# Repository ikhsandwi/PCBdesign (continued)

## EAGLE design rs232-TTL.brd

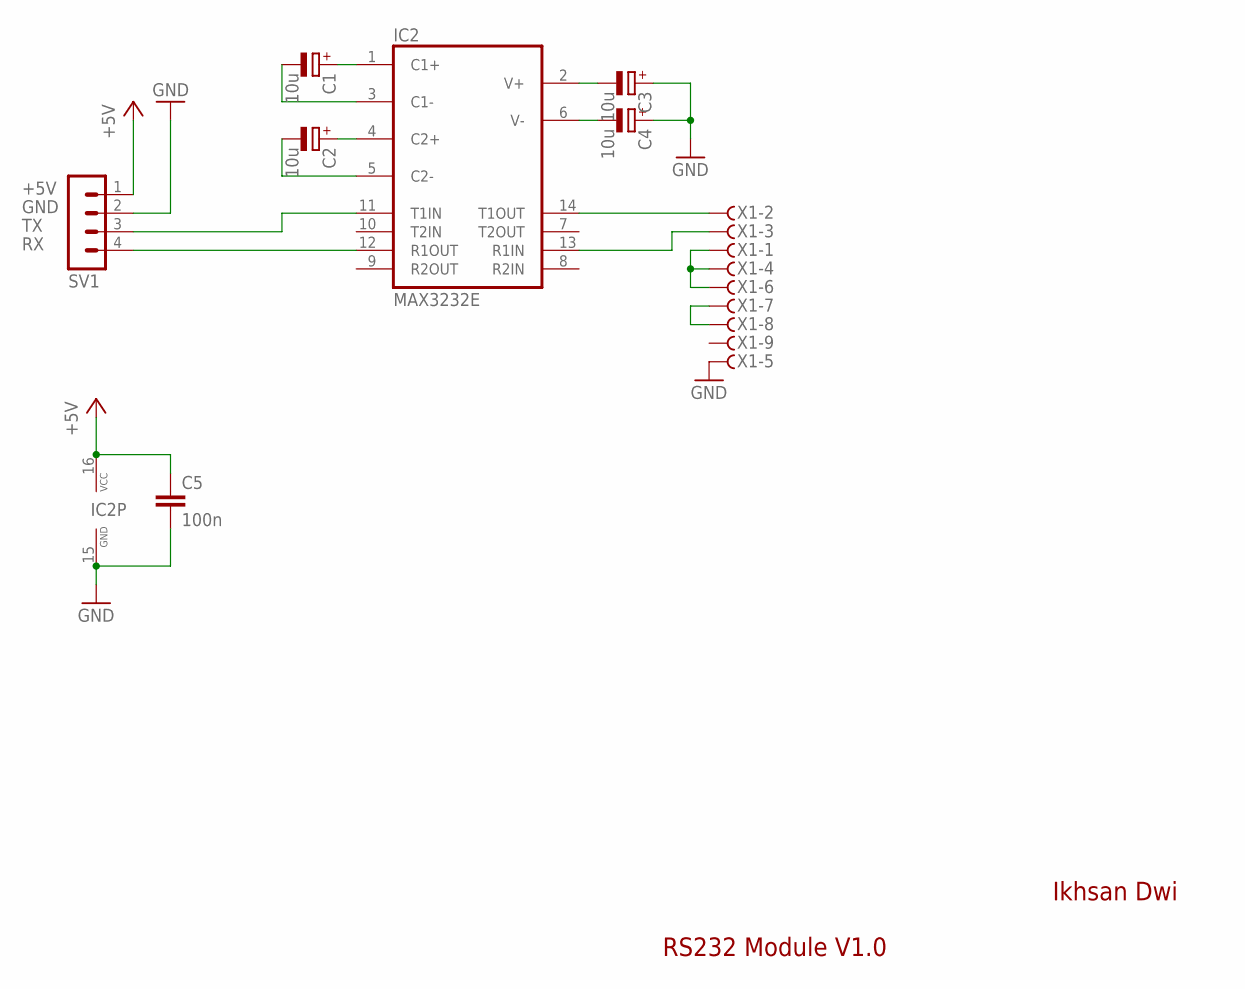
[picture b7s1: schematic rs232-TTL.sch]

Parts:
C1, C2, C3, C4: 10u; E2,5-6
C5: 100n; C050-024X044
IC2: MAX3232E; DIL16
SV1: MA04-1
X1: F09HS; F09H

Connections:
+5V: C5.1, IC2.16 (VCC), SV1.1
GND: C3.+, C4.+, C5.2, IC2.15 (GND), SV1.2, X1.5
unnamed: C1.-, IC2.3 (C1-)
unnamed: C1.+, IC2.1 (C1+)
unnamed: X1.1, X1.4, X1.6
unnamed: C2.+, IC2.4 (C2+)
unnamed: C2.-, IC2.5 (C2-)
unnamed: C3.-, IC2.2 (V+)
unnamed: C4.-, IC2.6 (V-)
unnamed: X1.7, X1.8
unnamed: IC2.14 (T1OUT), X1.2
unnamed: IC2.13 (R1IN), X1.3
RX: IC2.12 (R1OUT), SV1.4
TX: IC2.11 (T1IN), SV1.3

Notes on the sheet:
Ikhsan Dwi
RS232 Module V1.0

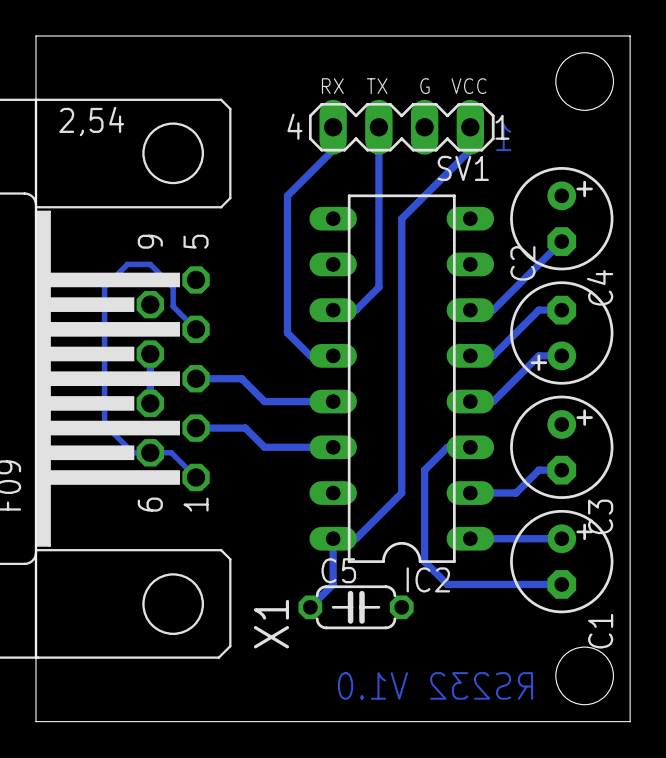
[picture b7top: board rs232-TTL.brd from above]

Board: 2 copper layers, 33.0 x 38.1 mm, 8 parts (0 on the bottom side), 14 nets.

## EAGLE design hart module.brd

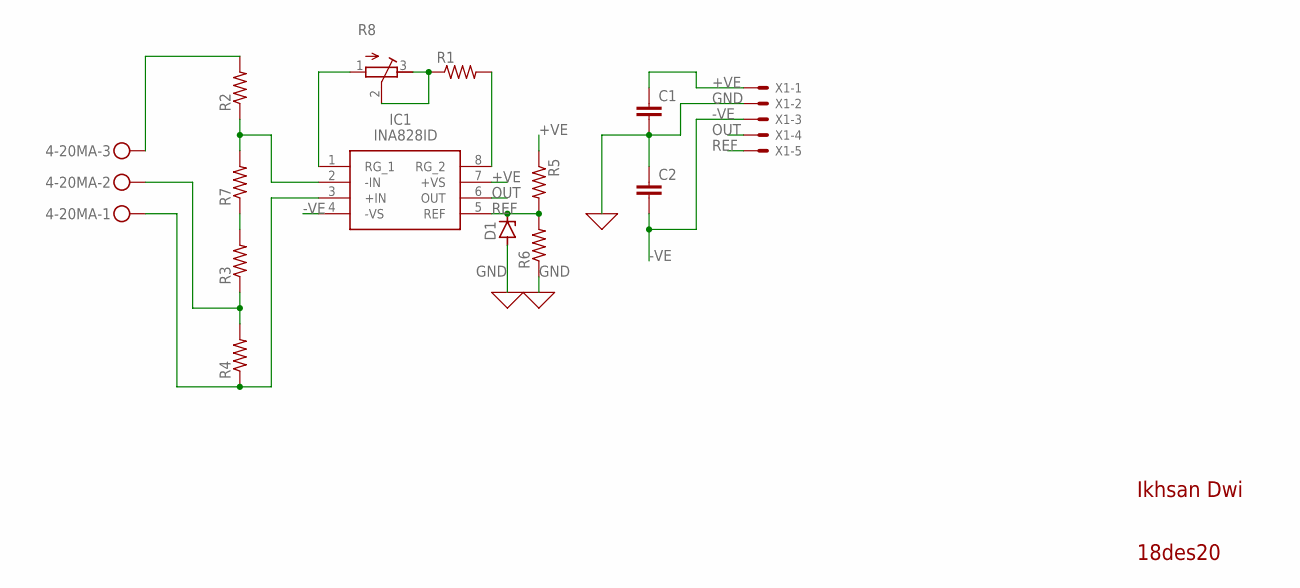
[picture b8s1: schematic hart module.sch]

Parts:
4-20MA: MKDSN1,5/3-5,08
C1, C2: C-EU025-025X050; C025-025X050
D1: ZENER-DIODEDO35Z10; DO35Z10
IC1: INA828ID; SOIC127P600X175-8N
R1, R2, R3, R4, R5, R6, R7: R-US_R1206W; R1206W
R8: R-TRIMM3339P; RTRIM3339P
X1: 22-23-2051

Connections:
+VE: C1.1, IC1.7 (+VS), R5.1, X1.1
-VE: C2.2, IC1.4 (-VS), X1.3
GND: C1.2, C2.1, D1.A, R6.1, X1.2
unnamed: R1.1, R8.2 (S), R8.3 (E)
unnamed: IC1.2 (-IN), R2.1, R7.2
unnamed: R3.2, R7.1
unnamed: 4-20MA.2, R3.1, R4.2
unnamed: 4-20MA.3, R2.2
unnamed: 4-20MA.1, IC1.3 (+IN), R4.1
unnamed: IC1.1 (RG_1), R8.1 (A)
unnamed: IC1.8 (RG_2), R1.2
OUT: IC1.6 (OUT), X1.4
REF: D1.C, IC1.5 (REF), R5.2, R6.2, X1.5

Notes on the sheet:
Ikhsan Dwi
18des20

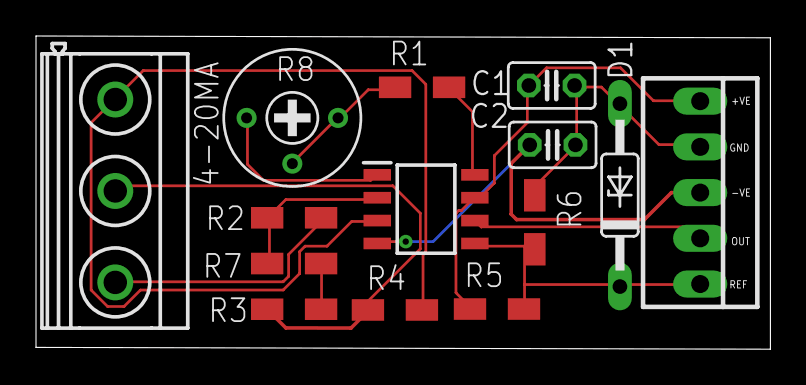
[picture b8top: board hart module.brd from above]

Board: 2 copper layers, 40.8 x 17.4 mm, 14 parts (0 on the bottom side), 13 nets.
